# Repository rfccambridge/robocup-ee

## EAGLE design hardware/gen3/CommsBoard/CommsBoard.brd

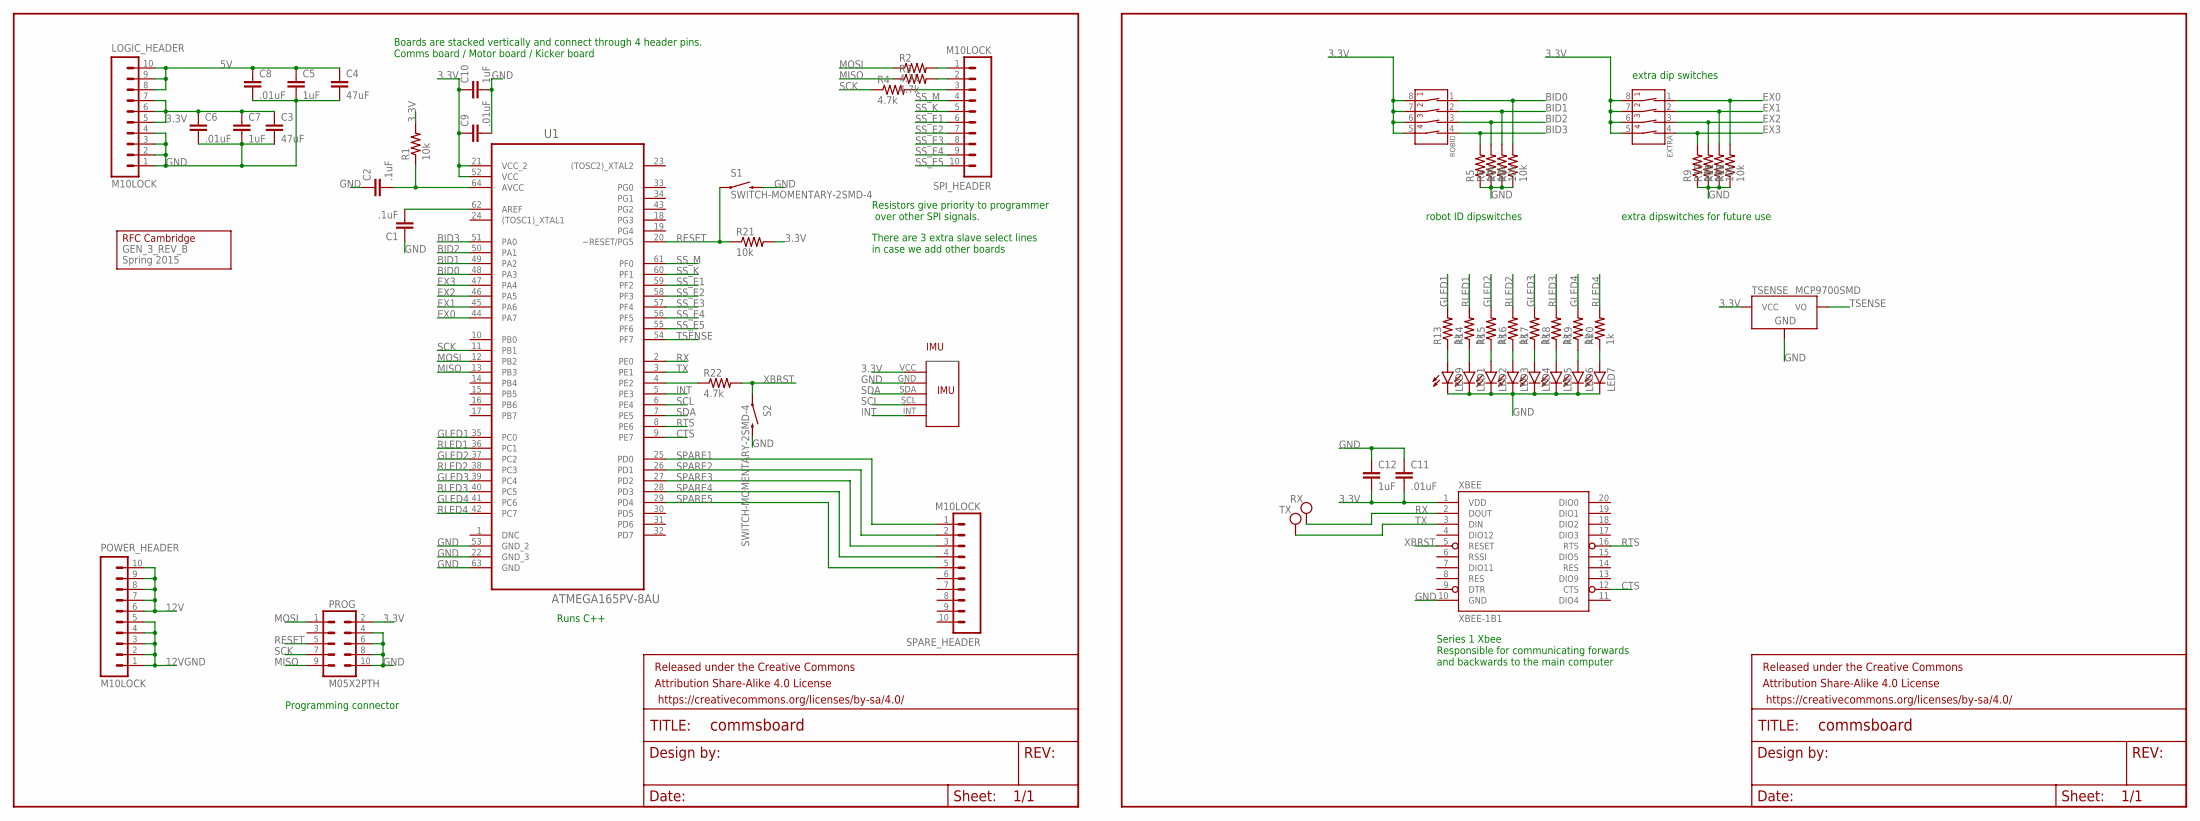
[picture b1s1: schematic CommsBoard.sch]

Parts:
C1, C2: .1uF; 0805
C3, C4: 47uF; 1206
C5, C7, C10, C12: 1uF; 0805
C6, C8, C9, C11: .01uF; 0805
EXTRA: 4-POS-DIP; 4-POS-DIP-SMD
FRAME1, FRAME2: FRAME-LETTER; CREATIVE_COMMONS
GEN_3_REV_B: Spring 2015; LOGO
IMU: MPU6050IMUMPU; MPU-6050IMU
LED1, LED2, LED3, LED4, LED5, LED6, LED7, LED9: LED1206; LED-1206
LOGIC_HEADER: M10LOCK; 1X10_LOCK
POWER_HEADER: M10LOCK; 1X10_LOCK
PROG: M05X2PTH; AVR_ICSP
R1, R5, R6, R7, R8, R9, R10, R11, R12, R21: 10k; 0805
R2, R3, R4, R22: 4.7k; 0805
R13, R14, R15, R16, R17, R18, R19, R20: 1k; 0805
ROBID: 4-POS-DIP; 4-POS-DIP-SMD
RX: TEST_PT; TESTING_PT
S1, S2: SWITCH-MOMENTARY-2SMD-4; TACTILE_SWITCH_TALL
SPARE_HEADER: M10LOCK; 1X10_LOCK
SPI_HEADER: M10LOCK; 1X10_LOCK
TSENSE: MCP9700SMD; SOT23-3
TX: TEST_PT; TESTING_PT
U1: ATMEGA165PV-8AU; QFP80P1600X1600X120-64N
XBEE: XBEE-1B1; XBEE-1

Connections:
3.3V: C3.1, C6.1, C7.1, C9.1, C10.1, C11.2, C12.2, EXTRA.5 (4B), EXTRA.6 (3B), EXTRA.7 (2B), EXTRA.8 (1B), IMU.VCC, LOGIC_HEADER.5, LOGIC_HEADER.6, LOGIC_HEADER.7, PROG.2, R1.2, R21.2, ROBID.5 (4B), ROBID.6 (3B), ROBID.7 (2B), ROBID.8 (1B), TSENSE.1 (VCC), U1.21 (VCC_2), U1.52 (VCC), XBEE.1 (VDD)
5V: C4.1, C5.1, C8.1, LOGIC_HEADER.8, LOGIC_HEADER.9, LOGIC_HEADER.10
12V: POWER_HEADER.6, POWER_HEADER.7, POWER_HEADER.8, POWER_HEADER.9, POWER_HEADER.10
12VGND: POWER_HEADER.1, POWER_HEADER.2, POWER_HEADER.3, POWER_HEADER.4, POWER_HEADER.5
BID0: R8.2, ROBID.1 (1A), U1.48 (PA3)
BID1: R7.2, ROBID.2 (2A), U1.49 (PA2)
BID2: R6.2, ROBID.3 (3A), U1.50 (PA1)
BID3: R5.2, ROBID.4 (4A), U1.51 (PA0)
CTS: U1.9 (PE7), XBEE.12 (CTS)
EX0: EXTRA.1 (1A), R12.2, U1.44 (PA7)
EX1: EXTRA.2 (2A), R11.2, U1.45 (PA6)
EX2: EXTRA.3 (3A), R10.2, U1.46 (PA5)
EX3: EXTRA.4 (4A), R9.2, U1.47 (PA4)
FILT: C2.2, R1.1, U1.64 (AVCC)
GLED1: R13.2, U1.35 (PC0)
GLED2: R15.2, U1.37 (PC2)
GLED3: R17.2, U1.39 (PC4)
GLED4: R19.2, U1.41 (PC6)
GND: C1.1, C2.1, C3.2, C4.2, C5.2, C6.2, C7.2, C8.2, C9.2, C10.2, C11.1, C12.1, IMU.GND, LED1.C, LED2.C, LED3.C, LED4.C, LED5.C, LED6.C, LED7.C, LED9.C, LOGIC_HEADER.1, LOGIC_HEADER.2, LOGIC_HEADER.3, LOGIC_HEADER.4, PROG.4, PROG.6, PROG.8, PROG.10, R5.1, R6.1, R7.1, R8.1, R9.1, R10.1, R11.1, R12.1, S1.B2 (2), S2.B2 (2), TSENSE.3 (GND), U1.22 (GND_3), U1.53 (GND_2), U1.63 (GND), XBEE.10 (GND)
INT: IMU.INT, U1.5 (PE3)
MISO: PROG.9, R3.1, U1.13 (PB3)
MOSI: PROG.1, R2.1, U1.12 (PB2)
unnamed: LED9.A, R13.1
unnamed: R22.1, U1.4 (PE2)
unnamed: LED1.A, R14.1
unnamed: LED2.A, R15.1
unnamed: LED3.A, R16.1
unnamed: LED4.A, R17.1
unnamed: LED5.A, R18.1
unnamed: LED6.A, R19.1
unnamed: LED7.A, R20.1
unnamed: C1.2, U1.62 (AREF)
PRE-MISO: R3.2, SPI_HEADER.2
PRE-MOSI: R2.2, SPI_HEADER.1
PRE-SCK: R4.2, SPI_HEADER.3
RESET: PROG.5, R21.1, S1.A2 (1), U1.20 (~RESET/PG5)
RLED1: R14.2, U1.36 (PC1)
RLED2: R16.2, U1.38 (PC3)
RLED3: R18.2, U1.40 (PC5)
RLED4: R20.2, U1.42 (PC7)
RTS: U1.8 (PE6), XBEE.16 (RTS)
RX: RX.P$1, U1.2 (PE0), XBEE.2 (DOUT)
SCK: PROG.7, R4.1, U1.11 (PB1)
SCL: IMU.SCL, U1.6 (PE4)
SDA: IMU.SDA, U1.7 (PE5)
SPARE1: SPARE_HEADER.1, U1.25 (PD0)
SPARE2: SPARE_HEADER.2, U1.26 (PD1)
SPARE3: SPARE_HEADER.3, U1.27 (PD2)
SPARE4: SPARE_HEADER.4, U1.28 (PD3)
SPARE5: SPARE_HEADER.5, U1.29 (PD4)
SS_E1: SPI_HEADER.6, U1.59 (PF2)
SS_E2: SPI_HEADER.7, U1.58 (PF3)
SS_E3: SPI_HEADER.8, U1.57 (PF4)
SS_E4: SPI_HEADER.9, U1.56 (PF5)
SS_E5: SPI_HEADER.10, U1.55 (PF6)
SS_K: SPI_HEADER.5, U1.60 (PF1)
SS_M: SPI_HEADER.4, U1.61 (PF0)
TSENSE: TSENSE.2 (VO), U1.54 (PF7)
TX: TX.P$1, U1.3 (PE1), XBEE.3 (DIN)
XBRST: R22.2, S2.A2 (1), XBEE.5 (RESET)

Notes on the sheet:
extra dip switches
Series 1 Xbee Responsible for communicating forwards and backwards to the main computer
robot ID dipswitches
extra dipswitches for future use
Resistors give priority to programmer over other SPI signals.
There are 3 extra slave select lines in case we add other boards
Runs C++
Programming connector
Boards are stacked vertically and connect through 4 header pins. Comms board / Motor board / Kicker board

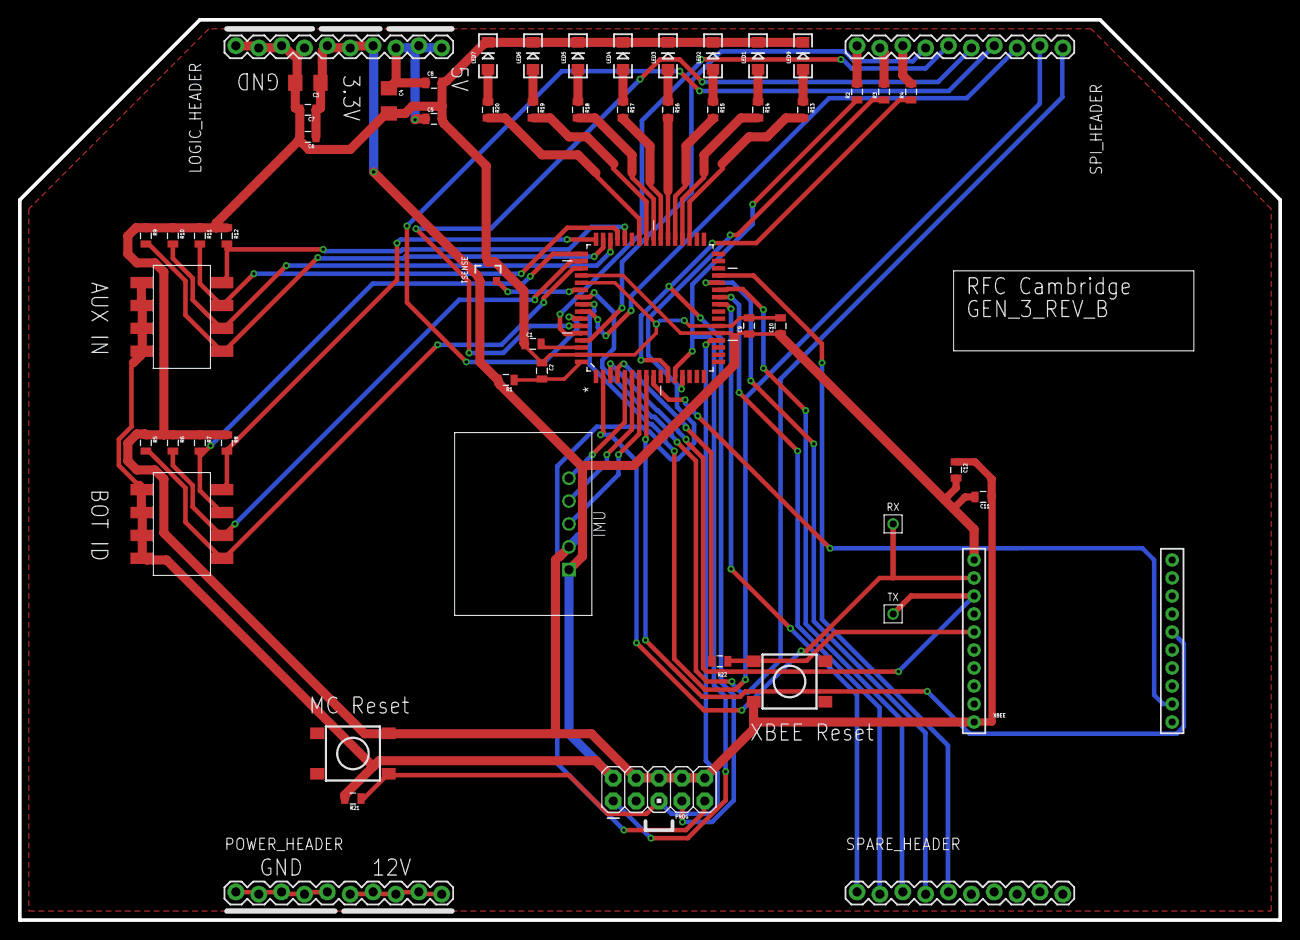
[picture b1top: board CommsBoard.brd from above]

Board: 2 copper layers, 140.0 x 100.0 mm, 60 parts (0 on the bottom side), 60 nets.

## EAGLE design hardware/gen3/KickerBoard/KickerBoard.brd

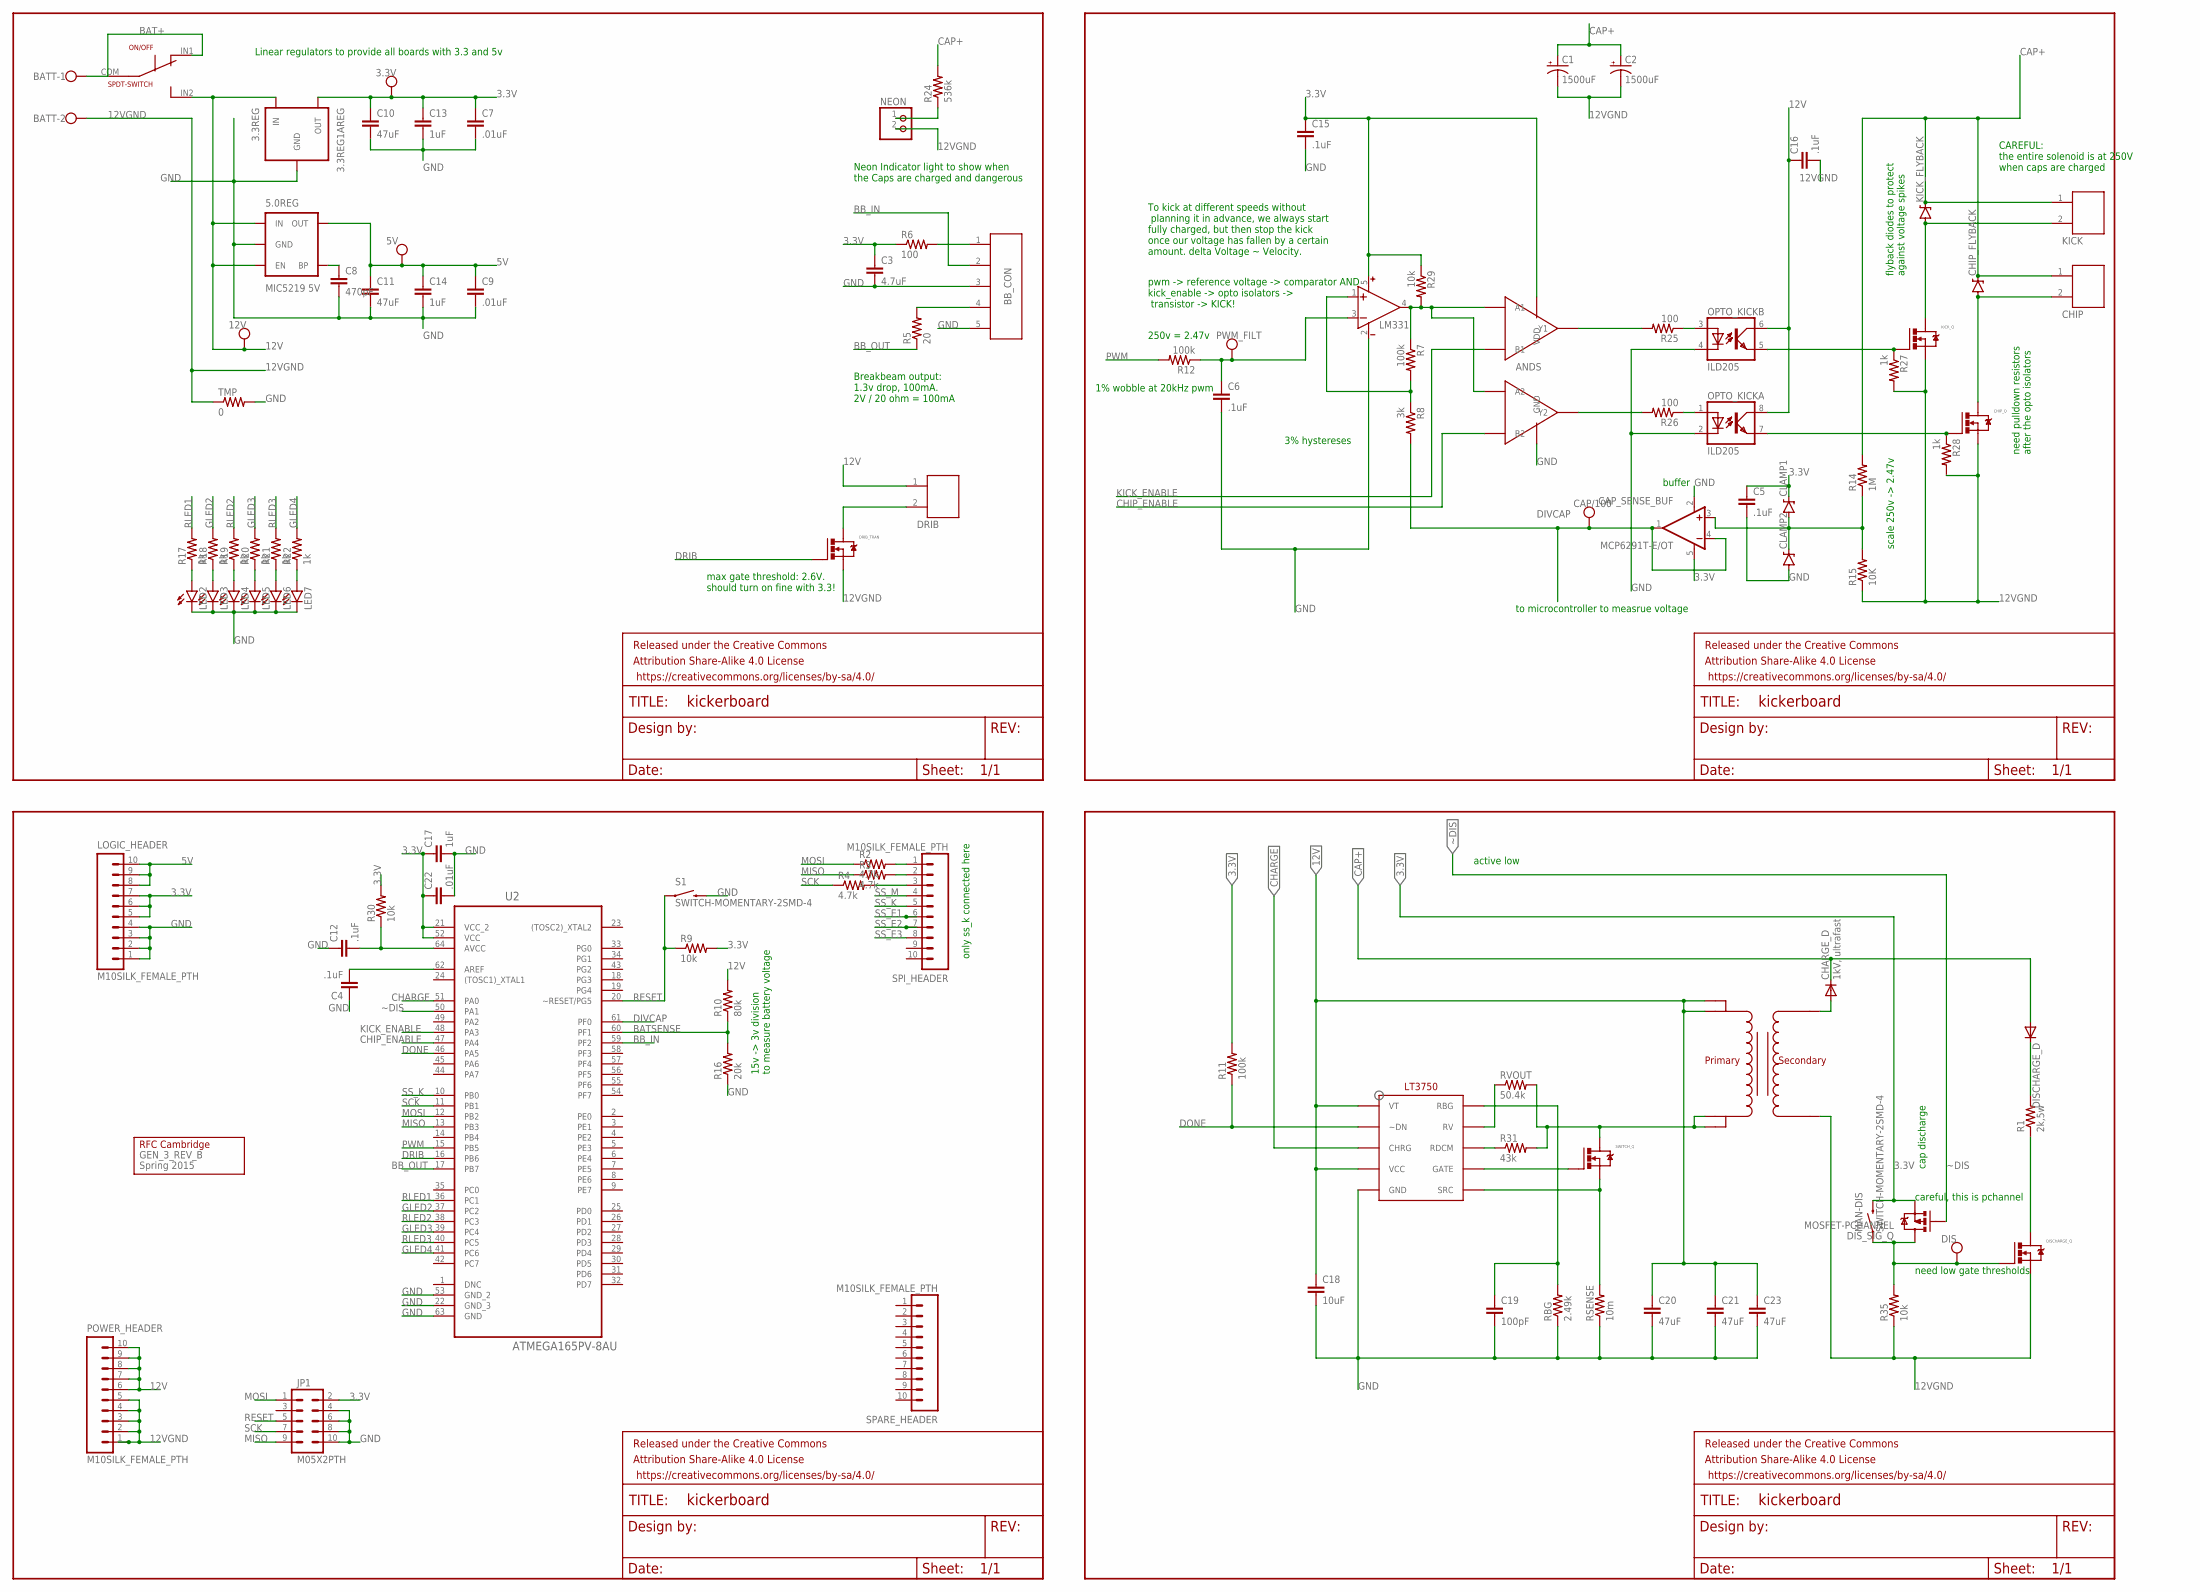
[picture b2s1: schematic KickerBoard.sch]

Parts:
3.3REG: 3.3REG1AREG; DPAK
3.3V, 5V, 12V: TEST_PT; TESTING_PT
5.0REG: MIC5219 5V; SOT23-5
ANDS: AND-DUAL; TSSOP8
BATT: W237-102
BB_CON: JST-5; JST-5-2MM
C1, C2: 1500uF; EB35D
C3: 4.7uF; 0805
C4, C5, C6, C12, C15, C16: .1uF; 0805
C7, C9, C22: .01uF; 0805
C8: 470pF; 0805
C10, C11, C20, C21, C23: 47uF; 1206
C13, C14, C17: 1uF; 0805
C18: 10uF; 0805
C19: 100pF; 0805
CAP/100: TEST_PT; TESTING_PT
CAP_COMP: LM331; SOT23-5
CAP_SENSE_BUF: MCP6291T-E/OT; SOT23-5
CHARGE_D: 1kV, ultrafast; DO214AC
CHARGE_U: LT3750; 10-MSOP
CHIP: JST-22MM; JST-2-2MM
CHIP_FLYBACK: DIODE-ZENERDO214AB; DO214AB
CHIP_Q: N-MOSFETDPAK; DPAK
CLAMP1, CLAMP2: DIODE-ZENERDO214AC; DO214AC
DIS: TEST_PT; TESTING_PT
DISCHARGE_D: DIODE-DO214AA; DO214AA
DISCHARGE_Q: N-MOSFETDPAK; DPAK
DIS_SIG_Q: MOSFET-PCHANNEL; SOT23-3
DRIB: JST-22MM; JST-2-2MM
DRIB_TRAN: N-MOSFETDPAK; DPAK
FRAME1, FRAME2, FRAME3, FRAME4: FRAME-LETTER; CREATIVE_COMMONS
GEN_3_REV_B: Spring 2015; LOGO
JP1: M05X2PTH; AVR_ICSP
KICK: JST-22MM; JST-2-2MM
KICK_FLYBACK: DIODE-ZENERDO214AB; DO214AB
KICK_Q: N-MOSFETDPAK; DPAK
LED2, LED3, LED4, LED5, LED6, LED7: LED1206; LED-1206
LOGIC_HEADER: M10SILK_FEMALE_PTH; 1X10
MAN-DIS: SWITCH-MOMENTARY-2SMD-4; TACTILE_SWITCH_TALL
NEON: PINHD-1X2; 1X02
ON/OFF: SPDT-SWITCH; CK_SWITCH
OPTO_KICK: ILD205; SOIC08
POWER_HEADER: M10SILK_FEMALE_PTH; 1X10
PWM_FILT: TEST_PT; TESTING_PT
R1: 2k,5w; 5WRESISTOR
R2, R3, R4: 4.7k; 0805
R5: 20; 0805
R6, R25, R26: 100; 0805
R7, R11, R12: 100k; 0805
R8: 3k; 0805
R9, R29, R30, R35: 10k; 0805
R10: 80k; 0805
R14: 1M; 0805
R15: 10K; 0805
R16: 20k; 0805
R17, R18, R19, R20, R21, R22, R27, R28: 1k; 0805
R24: 536k; 0805
R31: 43k; 0805
RBG: 2.49k; 0805
RSENSE: 10m; R2512
RVOUT: 50.4k; 0805
S1: SWITCH-MOMENTARY-2SMD-4; TACTILE_SWITCH_TALL
SPARE_HEADER: M10SILK_FEMALE_PTH; 1X10
SPI_HEADER: M10SILK_FEMALE_PTH; 1X10
SWITCH_Q: N-MOSFETDPAK; DPAK
TMP: 0; 0805
U2: ATMEGA165PV-8AU; QFP80P1600X1600X120-64N
U$1: 32052-TRANSFORMER; 10-TRANSFORMER

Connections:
3.3V: 3.3REG.SOURCE (OUT), 3.3V.P$1, ANDS.P$8 (VDD), C3.1, C5.1, C7.1, C10.1, C13.1, C15.1, C17.1, C22.1, CAP_COMP.5 (V+), CAP_SENSE_BUF.5 (V+), CLAMP1.C, DIS_SIG_Q.2 (S), JP1.2, LOGIC_HEADER.5, LOGIC_HEADER.6, LOGIC_HEADER.7, MAN-DIS.B2 (2), R6.1, R9.2, R11.2, R29.1, R30.2, U2.21 (VCC_2), U2.52 (VCC)
5V: 5.0REG.5 (OUT), 5V.P$1, C9.1, C11.1, C14.1, LOGIC_HEADER.8, LOGIC_HEADER.9, LOGIC_HEADER.10
12V: 3.3REG.GATE (IN), 5.0REG.1 (IN), 5.0REG.3 (EN), 12V.P$1, C16.1, C18.1, C20.1, C21.1, C23.1, CHARGE_U.P$1 (VT), CHARGE_U.P$4 (VCC), DRIB.1, ON/OFF.IN2 (P2), OPTO_KICK.6 (COL), OPTO_KICK.8 (COL), POWER_HEADER.6, POWER_HEADER.7, POWER_HEADER.8, POWER_HEADER.9, POWER_HEADER.10, R10.2, U$1.P$4, U$1.P$5
12VGND: BATT.2, C1.-, C2.-, C16.2, CHIP_Q.SOURCE (S), DISCHARGE_Q.SOURCE (S), DRIB_TRAN.SOURCE (S), KICK_Q.SOURCE (S), NEON.2, POWER_HEADER.1, POWER_HEADER.2, POWER_HEADER.3, POWER_HEADER.4, POWER_HEADER.5, R15.1, R27.2, R28.2, R35.1, TMP.1, U$1.P$10
AND_CHIP: ANDS.P$3 (Y2), R26.2
AND_KICK: ANDS.P$7 (Y1), R25.2
AREF: C4.2, U2.62 (AREF)
AVCC: C12.2, R30.1, U2.64 (AVCC)
BAT+: BATT.1, ON/OFF.COM, ON/OFF.IN1 (P1)
BATSENSE: R10.1, R16.2, U2.60 (PF1)
BB_IN: BB_CON.2, U2.59 (PF2)
BB_OUT: R5.1, U2.17 (PB7)
CAP+: C1.+, C2.+, CHARGE_D.C, CHIP.1, CHIP_FLYBACK.CATHODE (C), DISCHARGE_D.A, KICK.1, KICK_FLYBACK.CATHODE (C), R14.2, R24.2
CHARGE: CHARGE_U.P$3 (CHRG), U2.51 (PA0)
CHIP_ENABLE: ANDS.P$6 (B2), U2.47 (PA4)
COMP_OUT: ANDS.P$1 (A1), ANDS.P$5 (A2), CAP_COMP.4 (OUT), R7.1, R29.2
DISCHARGE_GATE: DIS.P$1, DISCHARGE_Q.GATE (G), DIS_SIG_Q.3 (D), MAN-DIS.A2 (1), R35.2
DIVCAP: CAP/100.P$1, CAP_SENSE_BUF.1 (OUT), CAP_SENSE_BUF.4 (-IN), R8.2, U2.61 (PF0)
DONE: CHARGE_U.P$2 (~DN), R11.1, U2.46 (PA5)
DRIB: DRIB_TRAN.GATE (G), U2.16 (PB6)
GATE_CHIP: CHIP_Q.GATE (G), OPTO_KICK.7 (EMIT), R28.1
GATE_KICK: KICK_Q.GATE (G), OPTO_KICK.5 (EMIT), R27.1
GLED2: R18.2, U2.37 (PC2)
GLED3: R20.2, U2.39 (PC4)
GLED4: R22.2, U2.41 (PC6)
GND: 3.3REG.DRAIN (GND), 5.0REG.2 (GND), ANDS.P$4 (GND), BB_CON.3, BB_CON.5, C3.2, C4.1, C5.2, C6.2, C7.2, C8.2, C9.2, C10.2, C11.2, C12.1, C13.2, C14.2, C15.2, C17.2, C18.2, C19.2, C20.2, C21.2, C22.2, C23.2, CAP_COMP.2 (V-), CAP_SENSE_BUF.2 (V-), CHARGE_U.P$5 (GND), CLAMP2.A, JP1.4, JP1.6, JP1.8, JP1.10, LED2.C, LED3.C, LED4.C, LED5.C, LED6.C, LED7.C, LOGIC_HEADER.1, LOGIC_HEADER.2, LOGIC_HEADER.3, LOGIC_HEADER.4, OPTO_KICK.2 (C), OPTO_KICK.4 (C), R16.1, RBG.1, RSENSE.1, S1.B2 (2), TMP.2, U2.22 (GND_3), U2.53 (GND_2), U2.63 (GND)
HYSTERESIS: CAP_COMP.1 (IN+), R7.2, R8.1
KICK_ENABLE: ANDS.P$2 (B1), U2.48 (PA3)
MISO: JP1.9, R3.1, U2.13 (PB3)
MOSI: JP1.1, R2.1, U2.12 (PB2)
unnamed: C6.1, CAP_COMP.3 (IN-), PWM_FILT.P$1, R12.1
unnamed: LED2.A, R17.1
unnamed: R3.2, SPI_HEADER.2
unnamed: R4.2, SPI_HEADER.3
unnamed: R31.2, RVOUT.2, SWITCH_Q.DRAIN (D), U$1.P$6, U$1.P$7
unnamed: C19.1, CHARGE_U.P$10 (RBG), RBG.2
unnamed: CHARGE_U.P$9 (RV), RVOUT.1
unnamed: CHARGE_U.P$7 (GATE), SWITCH_Q.GATE (G)
unnamed: CHARGE_U.P$8 (RDCM), R31.1
unnamed: R2.2, SPI_HEADER.1
unnamed: DISCHARGE_D.C, R1.P$2 (2)
unnamed: 5.0REG.4 (BP), C8.1
unnamed: DISCHARGE_Q.DRAIN (D), R1.P$1 (1)
unnamed: OPTO_KICK.3 (A), R25.1
unnamed: LED3.A, R18.1
unnamed: LED4.A, R19.1
unnamed: CHARGE_U.P$6 (SRC), RSENSE.2, SWITCH_Q.SOURCE (S)
unnamed: LED5.A, R20.1
unnamed: LED6.A, R21.1
unnamed: LED7.A, R22.1
unnamed: BB_CON.4, R5.2
unnamed: KICK.2, KICK_FLYBACK.ANODE (A), KICK_Q.DRAIN (D)
unnamed: CHIP.2, CHIP_FLYBACK.ANODE (A), CHIP_Q.DRAIN (D)
unnamed: OPTO_KICK.1 (A), R26.1
unnamed: BB_CON.1, R6.2
PWM: R12.2, U2.15 (PB5)
RESET: JP1.5, R9.1, S1.A2 (1), U2.20 (~RESET/PG5)
RLED1: R17.2, U2.36 (PC1)
RLED2: R19.2, U2.38 (PC3)
RLED3: R21.2, U2.40 (PC5)
SCK: JP1.7, R4.1, U2.11 (PB1)
SS_E1: SPI_HEADER.6
SS_E2: SPI_HEADER.7
SS_E3: SPI_HEADER.8
SS_K: SPI_HEADER.5, U2.10 (PB0)
SS_M: SPI_HEADER.4
TO_DRIB: DRIB.2, DRIB_TRAN.DRAIN (D)
TO_NEON: NEON.1, R24.1
TRANS_OUT: CHARGE_D.A, U$1.P$1
UNBUF_DIVCAP: CAP_SENSE_BUF.3 (+IN), CLAMP1.A, CLAMP2.C, R14.1, R15.2
~DIS: DIS_SIG_Q.1 (G), U2.50 (PA1)

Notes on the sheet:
max gate threshold: 2.6V. should turn on fine with 3.3!
careful, this is pchannel
scale 250v -> 2.47v
250v = 2.47v
active low
only ss_k connected here
to microcontroller to measrue voltage
15v -> 3v division to measure battery voltage
Linear regulators to provide all boards with 3.3 and 5v
Neon Indicator light to show when the Caps are charged and dangerous
flyback diodes to protect against voltage spikes
need pulldown resistors after the opto isolators
To kick at different speeds without planning it in advance, we always start fully charged, but then stop the kick once our voltage has fallen by a certain amount. delta Voltage ~ Velocity.
pwm -> reference voltage -> comparator AND kick_enable -> opto isolators -> transistor -> KICK!
cap discharge
Breakbeam output: 1.3v drop, 100mA. 2V / 20 ohm = 100mA
1% wobble at 20kHz pwm
buffer
3% hystereses
need low gate thresholds
CAREFUL: the entire solenoid is at 250V when caps are charged

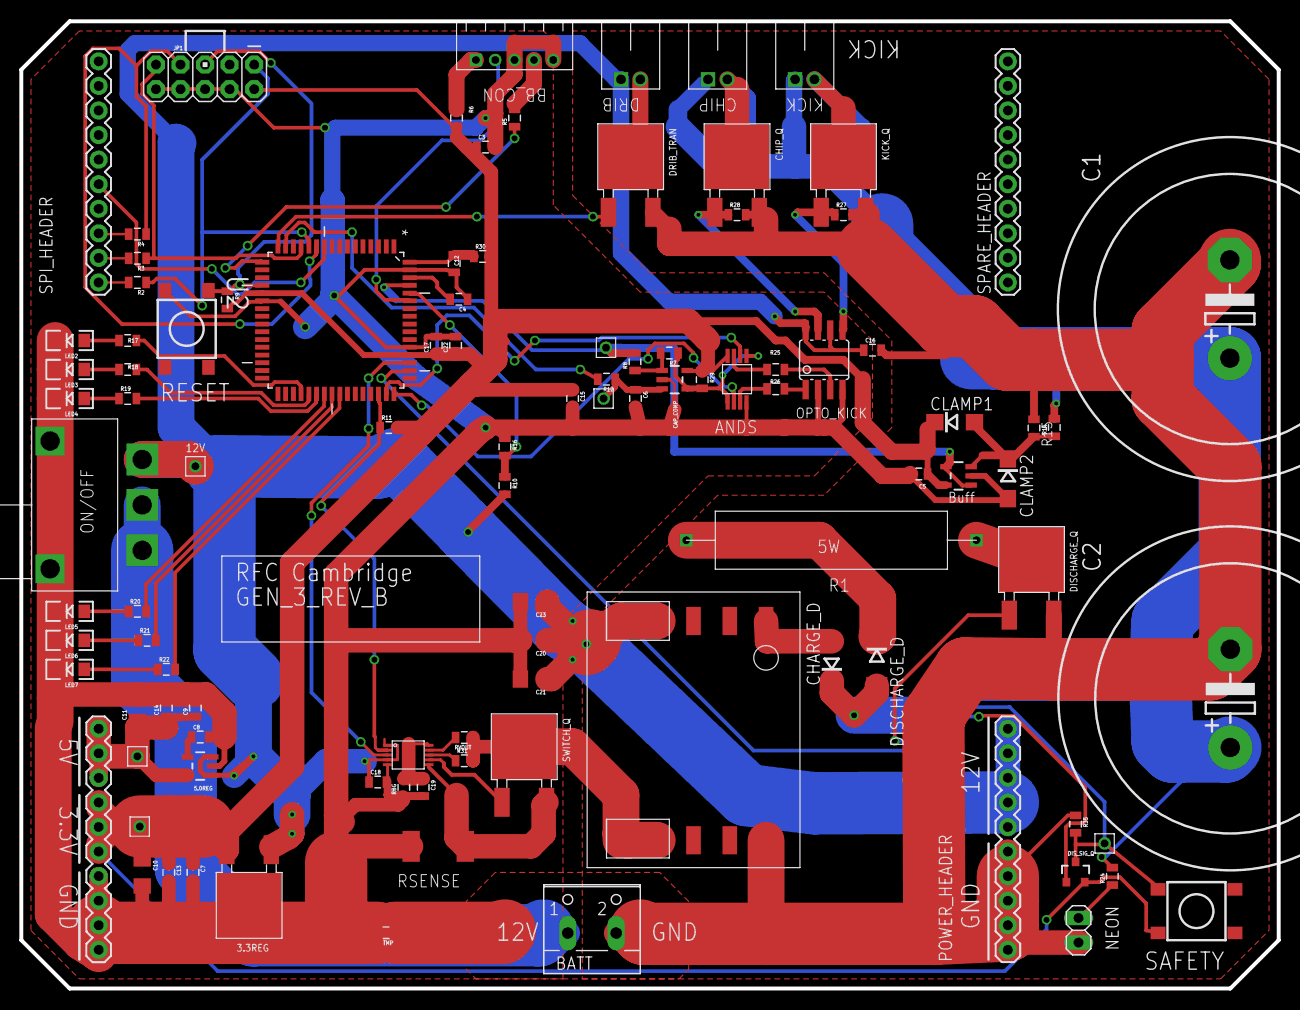
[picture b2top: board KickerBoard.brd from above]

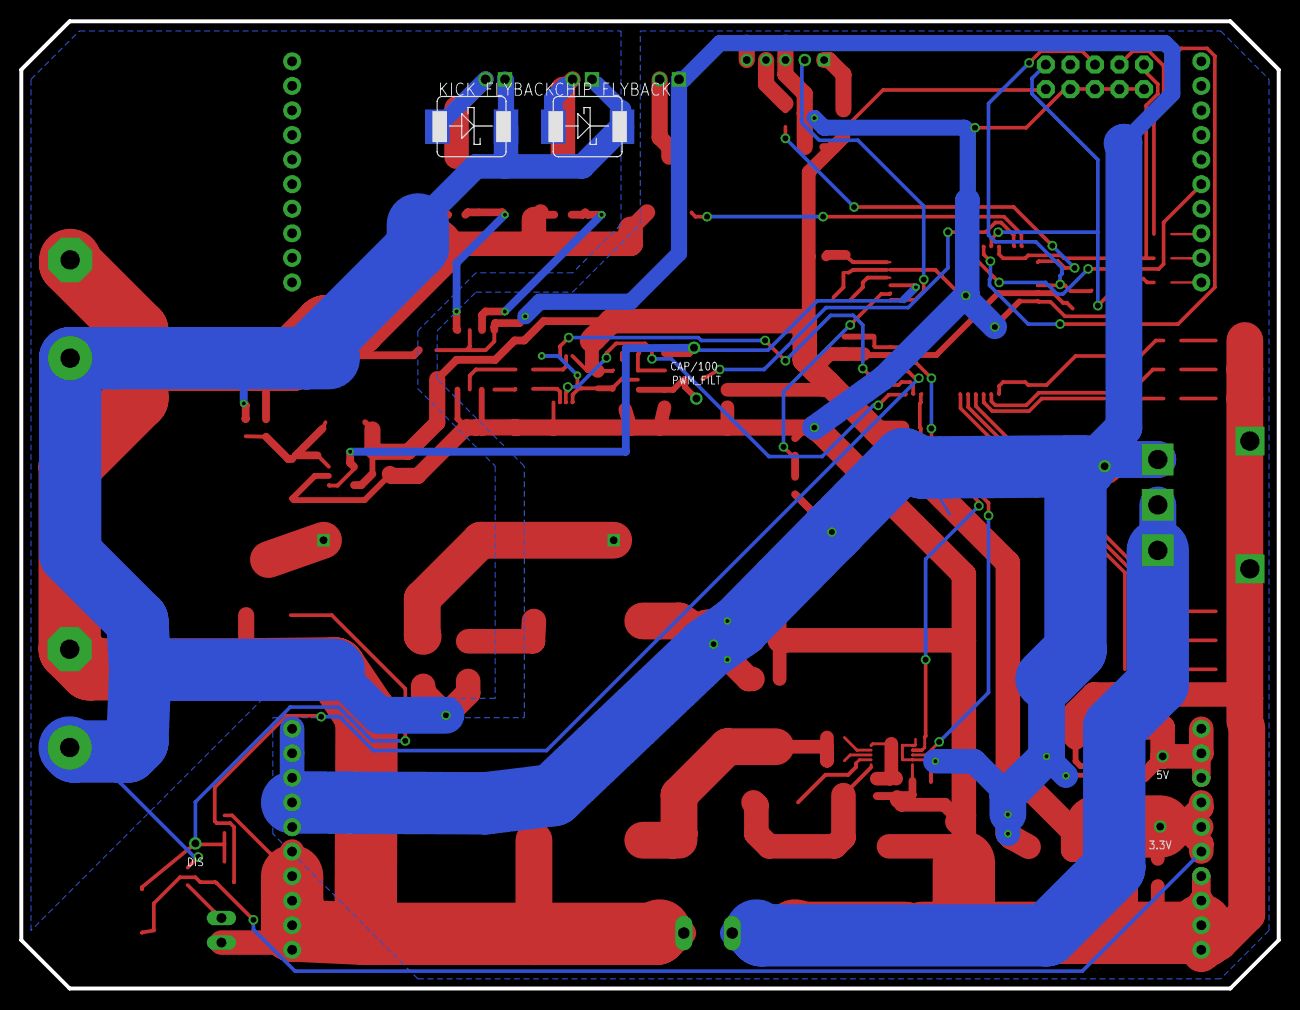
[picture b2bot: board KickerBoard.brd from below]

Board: 2 copper layers, 130.0 x 100.0 mm, 109 parts (2 on the bottom side), 67 nets.

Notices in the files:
parts and their libraries:
SparkFun-Aesthetics: Licensing: Creative Commons ShareAlike 4.0 International - https://creativecommons.org/licenses/by-sa/4.0
SparkFun-Aesthetics: Released under the Creative Commons Attribution Share-Alike 4.0 License
SparkFun-Aesthetics: https://creativecommons.org/licenses/by-sa/4.0
